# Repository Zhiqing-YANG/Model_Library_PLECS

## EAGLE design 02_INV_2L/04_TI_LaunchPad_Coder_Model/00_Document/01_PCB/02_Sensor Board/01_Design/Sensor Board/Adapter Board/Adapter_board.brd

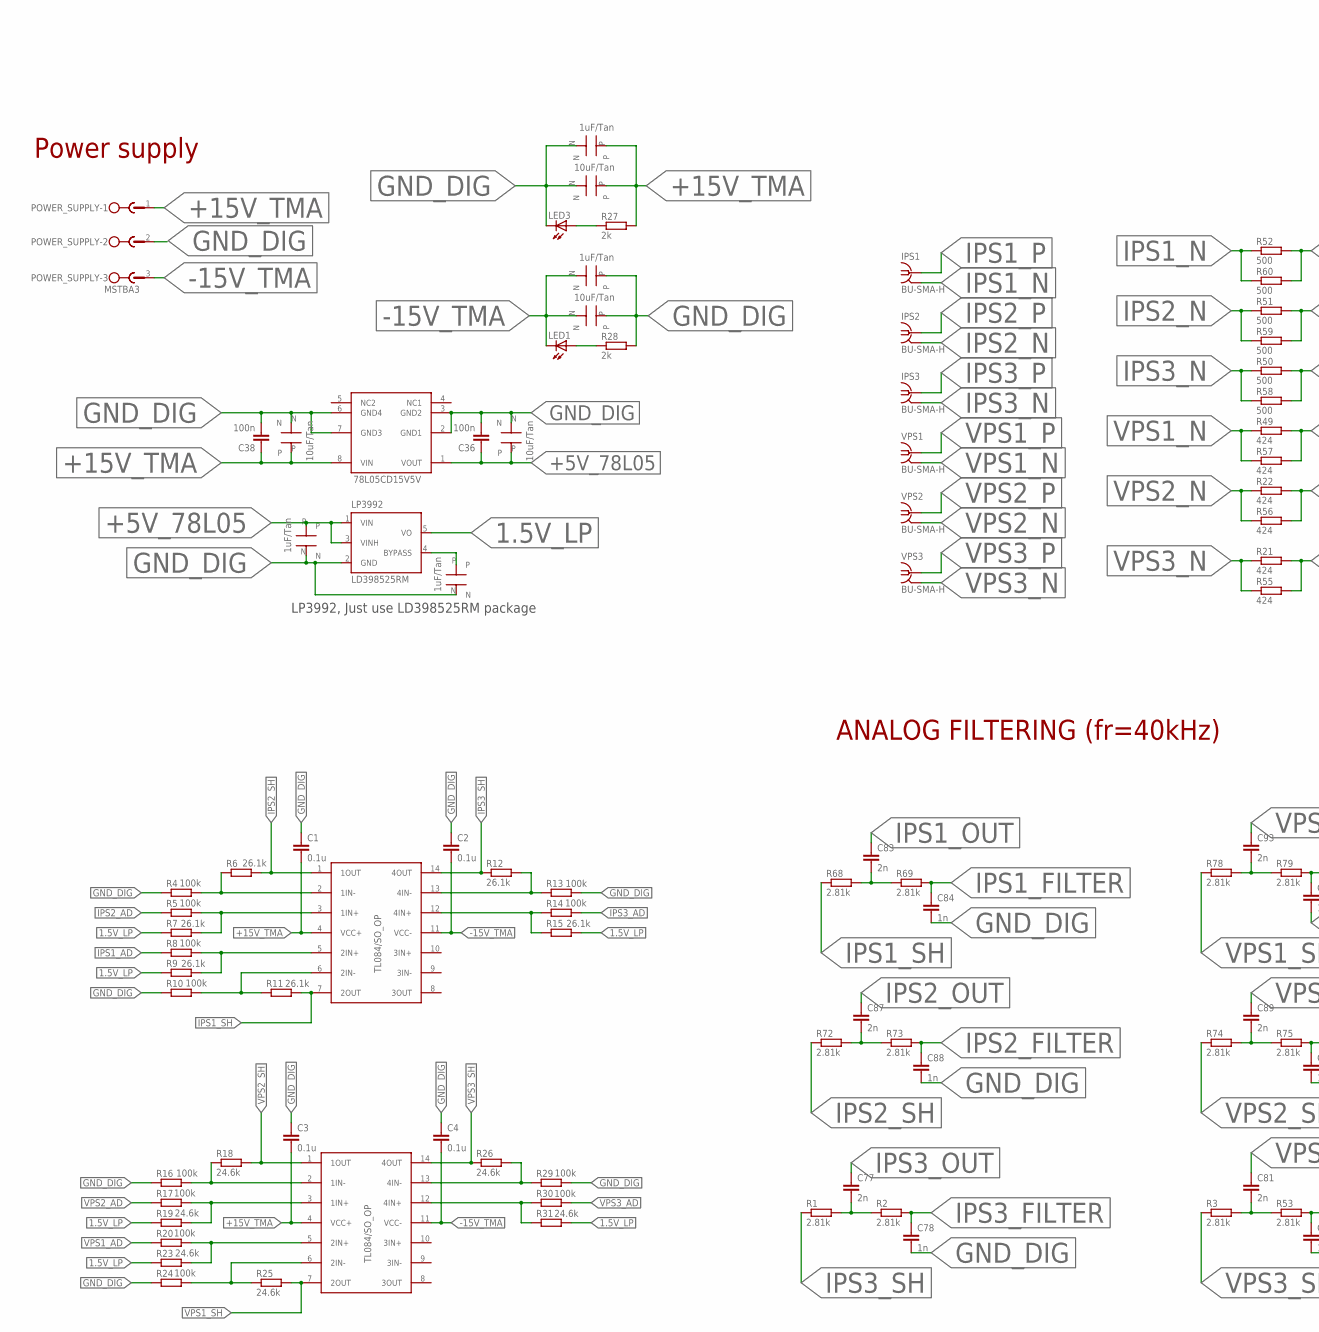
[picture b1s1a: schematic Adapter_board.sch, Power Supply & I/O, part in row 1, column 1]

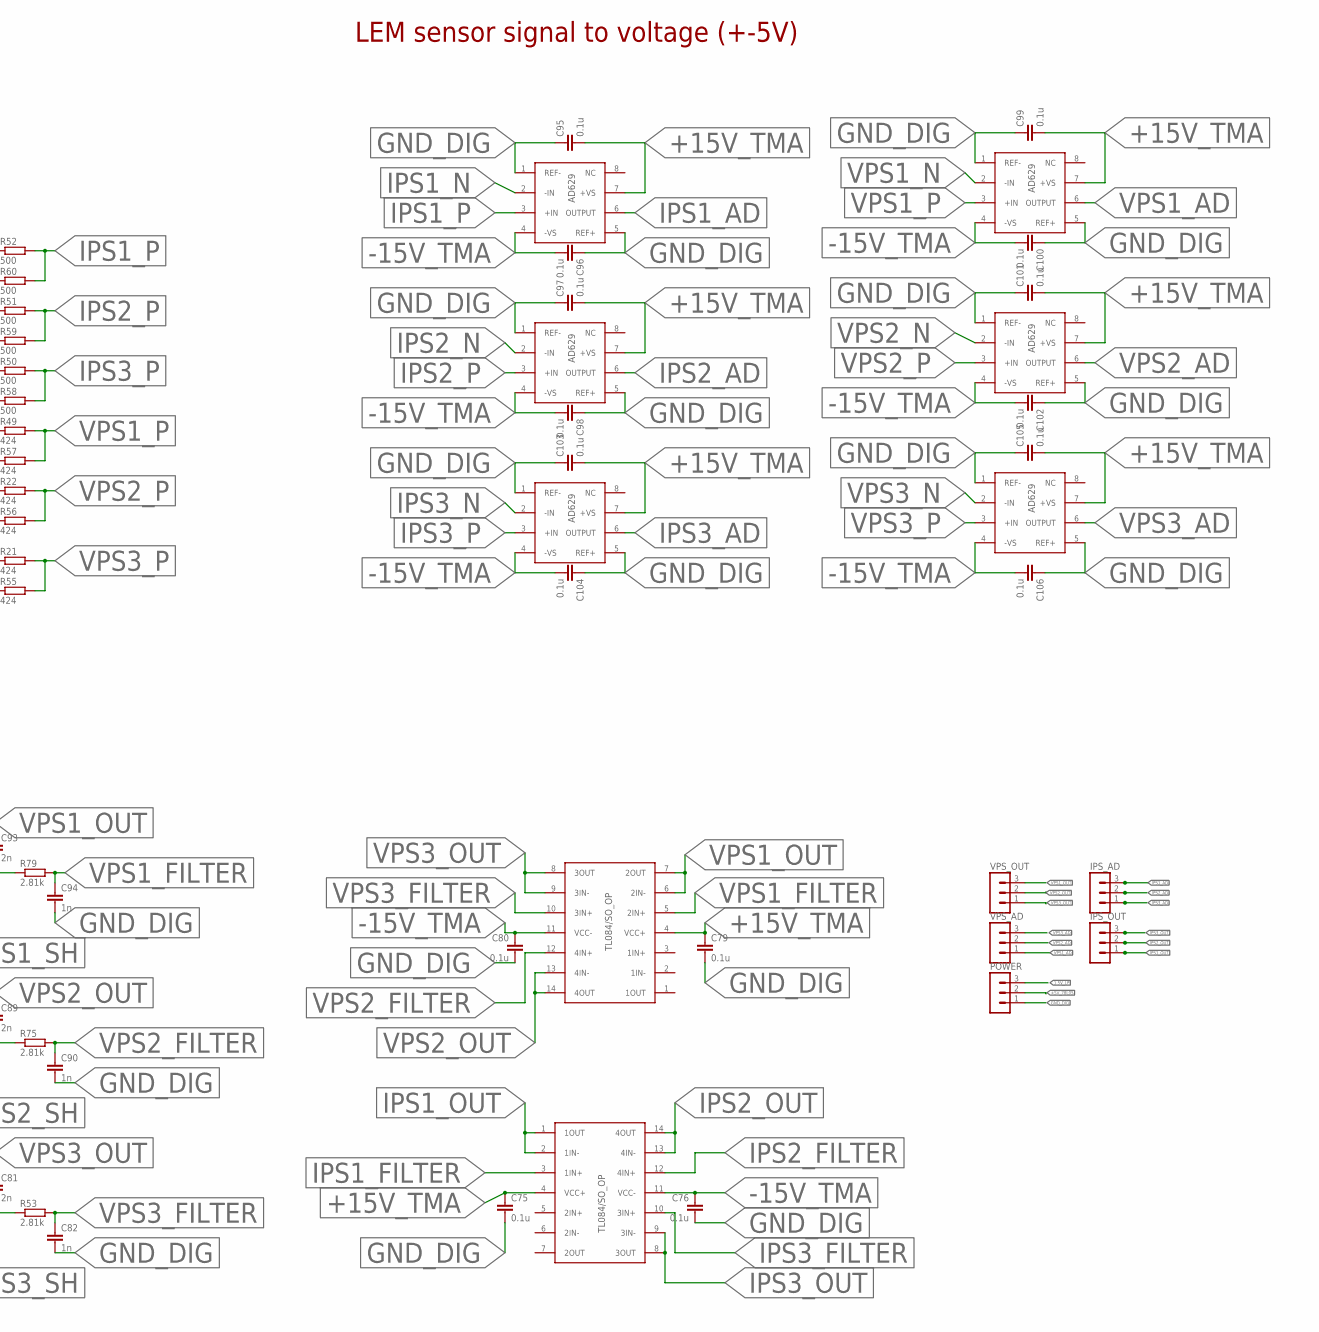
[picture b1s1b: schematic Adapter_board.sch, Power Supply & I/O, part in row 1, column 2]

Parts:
78L05: 78L05CD15V5VONLINE; 78L05CD15V5V_LIB
C1, C2, C3, C4, C75, C76, C79, C80, C95, C96, C97, C98, C99, C100, C101, C102, C103, C104, C105, C106: 0.1u; C0805
C36, C38: 100n; C0805
C37: TANTALUM_C_10UF_KEM
C77, C81, C83, C87, C89, C93: 2n; C0805
C78, C82, C84, C88, C90, C94: 1n; C0805
IPS1, IPS2, IPS3: BU-SMA-H
IPS_AD: MA03-1
IPS_OUT: MA03-1
LED1, LED3: LEDCHIPLED_0805; CHIPLED_0805
LP3992: LD398525RM; SOT23-5L
POWER: MA03-1
POWER_SUPPLY: MSTBA3
R1, R2, R3, R53, R68, R69, R72, R73, R74, R75, R78, R79: 2.81k; R0805
R4, R5, R8, R10, R13, R14, R16, R17, R20, R24, R29, R30: 100k; R0805
R6, R7, R9, R11, R12, R15: 26.1k; R0805
R18, R19, R23, R25, R26, R31: 24.6k; R0805
R21, R22, R49, R55, R56, R57: 424; R1206
R27, R28: 2k; R0805
R50, R51, R52, R58, R59, R60: 500; R1206
U$1, U$2, U$4, U$6: TL084/SO_OPONLINE; TL084/SO_OP_LIB
U$3, U$5, U$10, U$12: TANTALUM_C_1UF_KEMTANTALUM_C_1UF_KEM; TANTALUM_C_1UF_KEM
U$11, U$14, U$66: TANTALUM_C_10UF_KEM
U$24, U$27, U$28, U$29, U$30, U$31: AD629_DIFFAONLINE; AD629_DIFFA_LIB
VPS1, VPS2, VPS3: BU-SMA-H
VPS_AD: MA03-1
VPS_OUT: MA03-1

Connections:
1.5V_LP: LP3992.5 (VO), POWER.3, R7.1, R9.1, R15.2, R19.1, R23.1, R31.2
+5V_78L05: 78L05.1 (VOUT), C36.1, C37.P, LP3992.1 (VIN), LP3992.3 (VINH), POWER.2, U$3.P
+15V_TMA: 78L05.8 (VIN), C1.2, C3.2, C38.1, C75.1, C79.1, C95.2, C97.2, C99.2, C101.2, C103.2, C105.2, POWER_SUPPLY.1, R27.2, U$1.4 (VCC+), U$2.4 (VCC+), U$4.4 (VCC+), U$6.4 (VCC+), U$10.P, U$11.P, U$24.7 (+VS), U$27.7 (+VS), U$28.7 (+VS), U$29.7 (+VS), U$30.7 (+VS), U$31.7 (+VS), U$66.P
-15V_TMA: C2.2, C4.2, C76.1, C80.1, C96.2, C98.2, C100.2, C102.2, C104.2, C106.2, LED1.C, POWER_SUPPLY.3, U$1.11 (VCC-), U$2.11 (VCC-), U$4.11 (VCC-), U$6.11 (VCC-), U$12.N, U$14.N, U$24.4 (-VS), U$27.4 (-VS), U$28.4 (-VS), U$29.4 (-VS), U$30.4 (-VS), U$31.4 (-VS)
GND_DIG: 78L05.2 (GND1), 78L05.3 (GND2), 78L05.6 (GND4), 78L05.7 (GND3), C1.1, C2.1, C3.1, C4.1, C36.2, C37.N, C38.2, C75.2, C76.2, C78.2, C79.2, C80.2, C82.2, C84.2, C88.2, C90.2, C94.2, C95.1, C96.1, C97.1, C98.1, C99.1, C100.1, C101.1, C102.1, C103.1, C104.1, C105.1, C106.1, LED3.C, LP3992.2 (GND), POWER.1, POWER_SUPPLY.2, R4.1, R10.1, R13.2, R16.1, R24.1, R28.2, R29.2, U$3.N, U$5.N, U$10.N, U$11.N, U$12.P, U$14.P, U$24.1 (REF-), U$24.5 (REF+), U$27.1 (REF-), U$27.5 (REF+), U$28.1 (REF-), U$28.5 (REF+), U$29.1 (REF-), U$29.5 (REF+), U$30.1 (REF-), U$30.5 (REF+), U$31.1 (REF-), U$31.5 (REF+), U$66.N
IPS1_AD: IPS_AD.3, R8.1, U$24.6 (OUTPUT)
IPS1_FILTER: C84.1, R69.2, U$4.3 (1IN+)
IPS1_N: IPS1.2, IPS1.3 (2), IPS1.4 (2), IPS1.5 (2), R52.1, R60.1, U$24.2 (-IN)
IPS1_OUT: C83.1, IPS_OUT.1, U$4.1 (1OUT), U$4.2 (1IN-)
IPS1_P: IPS1.1, R52.2, R60.2, U$24.3 (+IN)
IPS1_SH: R11.2, R68.1, U$1.7 (2OUT)
IPS2_AD: IPS_AD.2, R5.1, U$27.6 (OUTPUT)
IPS2_FILTER: C88.1, R73.2, U$4.12 (4IN+)
IPS2_N: IPS2.2, IPS2.3 (2), IPS2.4 (2), IPS2.5 (2), R51.1, R59.1, U$27.2 (-IN)
IPS2_OUT: C87.1, IPS_OUT.2, U$4.13 (4IN-), U$4.14 (4OUT)
IPS2_P: IPS2.1, R51.2, R59.2, U$27.3 (+IN)
IPS2_SH: R6.2, R72.1, U$1.1 (1OUT)
IPS3_AD: IPS_AD.1, R14.2, U$30.6 (OUTPUT)
IPS3_FILTER: C78.1, R2.2, U$4.10 (3IN+)
IPS3_N: IPS3.2, IPS3.3 (2), IPS3.4 (2), IPS3.5 (2), R50.1, R58.1, U$30.2 (-IN)
IPS3_OUT: C77.1, IPS_OUT.3, U$4.8 (3OUT), U$4.9 (3IN-)
IPS3_P: IPS3.1, R50.2, R58.2, U$30.3 (+IN)
IPS3_SH: R1.1, R12.1, U$1.14 (4OUT)
unnamed: LP3992.4 (BYPASS), U$5.P
unnamed: R4.2, R6.1, U$1.2 (1IN-)
unnamed: R5.2, R7.2, U$1.3 (1IN+)
unnamed: R16.2, R18.1, U$2.2 (1IN-)
unnamed: R10.2, R11.1, U$1.6 (2IN-)
unnamed: R8.2, R9.2, U$1.5 (2IN+)
unnamed: R17.2, R19.2, U$2.3 (1IN+)
unnamed: C77.2, R1.2, R2.1
unnamed: C81.2, R3.2, R53.1
unnamed: C83.2, R68.2, R69.1
unnamed: LED3.A, R27.1
unnamed: LED1.A, R28.1
unnamed: C87.2, R72.2, R73.1
unnamed: R20.2, R23.2, U$2.5 (2IN+)
unnamed: C89.2, R74.2, R75.1
unnamed: C93.2, R78.2, R79.1
unnamed: R12.2, R13.1, U$1.13 (4IN-)
unnamed: R14.1, R15.1, U$1.12 (4IN+)
unnamed: R24.2, R25.1, U$2.6 (2IN-)
unnamed: R26.2, R29.1, U$2.13 (4IN-)
unnamed: R30.1, R31.1, U$2.12 (4IN+)
VPS1_AD: R20.1, U$28.6 (OUTPUT), VPS_AD.1
VPS1_FILTER: C94.1, R79.2, U$6.5 (2IN+)
VPS1_N: R49.1, R57.1, U$28.2 (-IN), VPS1.2, VPS1.3 (2), VPS1.4 (2), VPS1.5 (2)
VPS1_OUT: C93.1, U$6.6 (2IN-), U$6.7 (2OUT), VPS_OUT.3
VPS1_P: R49.2, R57.2, U$28.3 (+IN), VPS1.1
VPS1_SH: R25.2, R78.1, U$2.7 (2OUT)
VPS2_AD: R17.1, U$29.6 (OUTPUT), VPS_AD.2
VPS2_FILTER: C90.1, R75.2, U$6.12 (4IN+)
VPS2_N: R22.1, R56.1, U$29.2 (-IN), VPS2.2, VPS2.3 (2), VPS2.4 (2), VPS2.5 (2)
VPS2_OUT: C89.1, U$6.13 (4IN-), U$6.14 (4OUT), VPS_OUT.2
VPS2_P: R22.2, R56.2, U$29.3 (+IN), VPS2.1
VPS2_SH: R18.2, R74.1, U$2.1 (1OUT)
VPS3_AD: R30.2, U$31.6 (OUTPUT), VPS_AD.3
VPS3_FILTER: C82.1, R53.2, U$6.10 (3IN+)
VPS3_N: R21.1, R55.1, U$31.2 (-IN), VPS3.2, VPS3.3 (2), VPS3.4 (2), VPS3.5 (2)
VPS3_OUT: C81.1, U$6.8 (3OUT), U$6.9 (3IN-), VPS_OUT.1
VPS3_P: R21.2, R55.2, U$31.3 (+IN), VPS3.1
VPS3_SH: R3.1, R26.1, U$2.14 (4OUT)

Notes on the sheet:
Power supply
ANALOG FILTERING (fr=40kHz)
LEM sensor signal to voltage (+-5V)
LP3992, Just use LD398525RM package

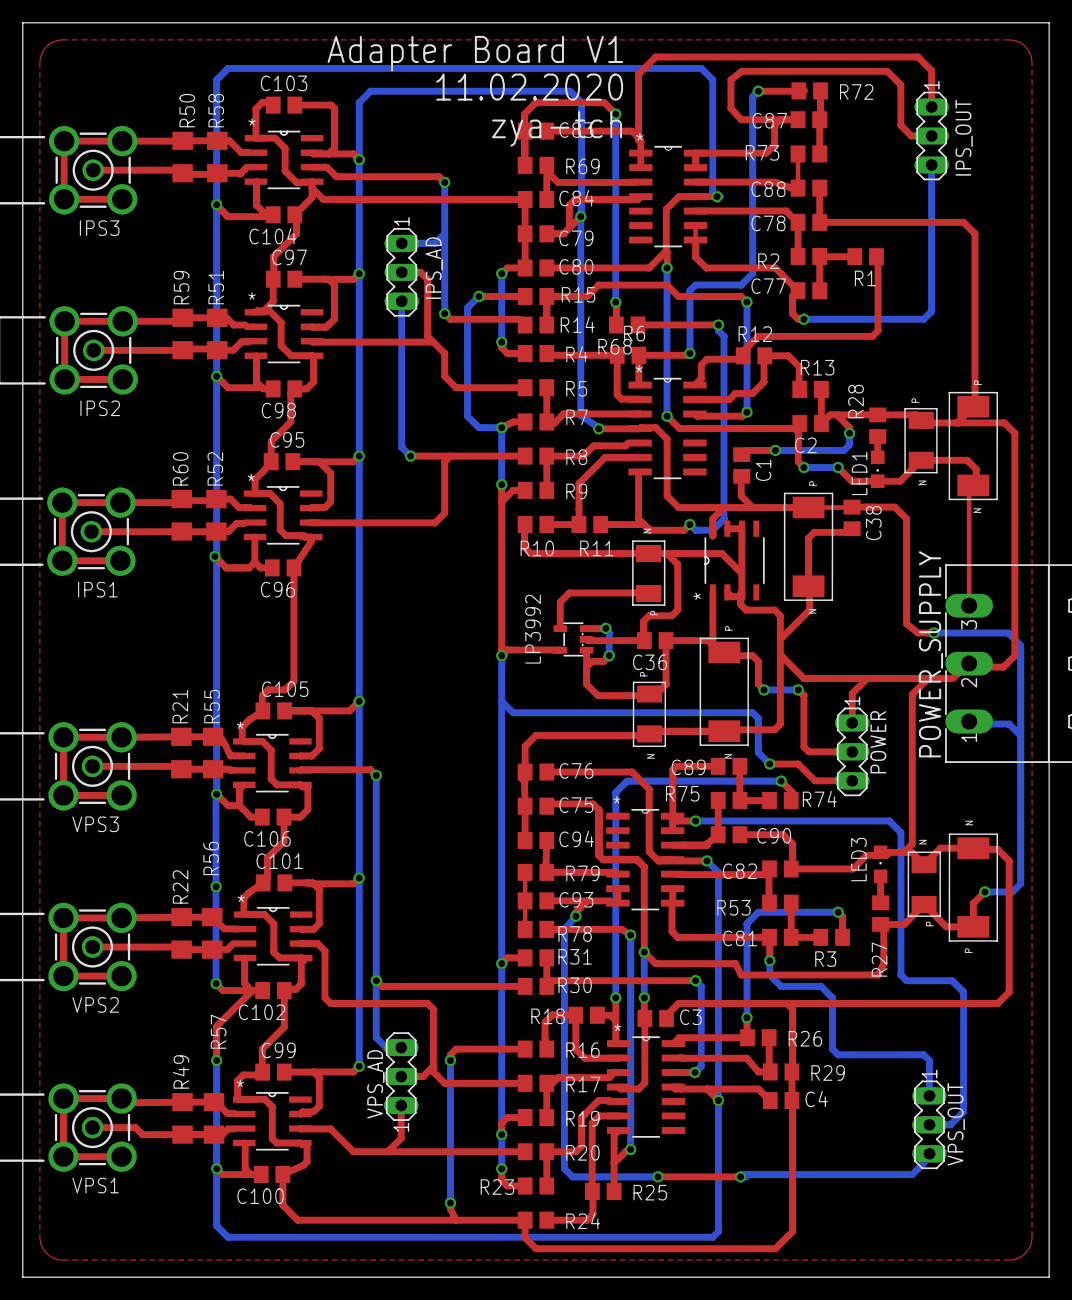
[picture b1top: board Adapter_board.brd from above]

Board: 2 copper layers, 90.0 x 110.0 mm, 118 parts (0 on the bottom side), 62 nets.

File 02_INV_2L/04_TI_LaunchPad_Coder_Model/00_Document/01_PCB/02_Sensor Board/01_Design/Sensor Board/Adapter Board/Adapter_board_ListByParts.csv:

"Part","Value","Attributes","Package","Description","Part Num"
"78L05","78L05CD15V5VONLINE","","78L05CD15V5V_LIB","78L05CD 15 V- 5 V voltage regulator","*"
"C1","0.1u","","C0805","CAPACITOR, European symbol","*"
"C2","0.1u","","C0805","CAPACITOR, European symbol","*"
"C3","0.1u","","C0805","CAPACITOR, European symbol","*"
"C4","0.1u","","C0805","CAPACITOR, European symbol","*"
"C36","100n","","C0805","CAPACITOR, European symbol","*"
"C37","TANTALUM_C_10UF_KEM","","TANTALUM_C_10UF_KEM","","*"
"C38","100n","","C0805","CAPACITOR, European symbol","*"
"C75","0.1u","","C0805","CAPACITOR, European symbol","*"
"C76","0.1u","","C0805","CAPACITOR, European symbol","*"
"C77","2n","","C0805","CAPACITOR, European symbol","*"
"C78","1n","","C0805","CAPACITOR, European symbol","*"
"C79","0.1u","","C0805","CAPACITOR, European symbol","*"
"C80","0.1u","","C0805","CAPACITOR, European symbol","*"
"C81","2n","","C0805","CAPACITOR, European symbol","*"
"C82","1n","","C0805","CAPACITOR, European symbol","*"
"C83","2n","","C0805","CAPACITOR, European symbol","*"
"C84","1n","","C0805","CAPACITOR, European symbol","*"
"C87","2n","","C0805","CAPACITOR, European symbol","*"
"C88","1n","","C0805","CAPACITOR, European symbol","*"
"C89","2n","","C0805","CAPACITOR, European symbol","*"
"C90","1n","","C0805","CAPACITOR, European symbol","*"
"C93","2n","","C0805","CAPACITOR, European symbol","*"
"C94","1n","","C0805","CAPACITOR, European symbol","*"
"C95","0.1u","","C0805","CAPACITOR, European symbol","*"
"C96","0.1u","","C0805","CAPACITOR, European symbol","*"
"C97","0.1u","","C0805","CAPACITOR, European symbol","*"
"C98","0.1u","","C0805","CAPACITOR, European symbol","*"
"C99","0.1u","","C0805","CAPACITOR, European symbol","*"
"C100","0.1u","","C0805","CAPACITOR, European symbol","*"
"C101","0.1u","","C0805","CAPACITOR, European symbol","*"
"C102","0.1u","","C0805","CAPACITOR, European symbol","*"
"C103","0.1u","","C0805","CAPACITOR, European symbol","*"
"C104","0.1u","","C0805","CAPACITOR, European symbol","*"
"C105","0.1u","","C0805","CAPACITOR, European symbol","*"
"C106","0.1u","","C0805","CAPACITOR, European symbol","*"
"IPS1","BU-SMA-H","","BU-SMA-H","FEMALE SMA CONNECTOR","*"
"IPS2","BU-SMA-H","","BU-SMA-H","FEMALE SMA CONNECTOR","*"
"IPS3","BU-SMA-H","","BU-SMA-H","FEMALE SMA CONNECTOR","*"
"IPS_AD","","","MA03-1","PIN HEADER","*"
"IPS_OUT","","","MA03-1","PIN HEADER","*"
"LED1","","","CHIPLED_0805","LED","*"
"LED3","","","CHIPLED_0805","LED","*"
"LP3992","LD398525RM","","SOT23-5L","Ultra low drop and low noise BiCMOS voltage regulators","*"
"POWER","","","MA03-1","PIN HEADER","*"
"POWER_SUPPLY","MSTBA3","","MSTBA3","PHOENIX","1757255"
"R1","2.81k","","R0805","RESISTOR, European symbol","*"
"R2","2.81k","","R0805","RESISTOR, European symbol","*"
"R3","2.81k","","R0805","RESISTOR, European symbol","*"
"R4","100k","","R0805","RESISTOR, European symbol","*"
"R5","100k","","R0805","RESISTOR, European symbol","*"
"R6","26.1k","","R0805","RESISTOR, European symbol","*"
"R7","26.1k","","R0805","RESISTOR, European symbol","*"
"R8","100k","","R0805","RESISTOR, European symbol","*"
"R9","26.1k","","R0805","RESISTOR, European symbol","*"
"R10","100k","","R0805","RESISTOR, European symbol","*"
"R11","26.1k","","R0805","RESISTOR, European symbol","*"
"R12","26.1k","","R0805","RESISTOR, European symbol","*"
"R13","100k","","R0805","RESISTOR, European symbol","*"
"R14","100k","","R0805","RESISTOR, European symbol","*"
"R15","26.1k","","R0805","RESISTOR, European symbol","*"
"R16","100k","","R0805","RESISTOR, European symbol","*"
"R17","100k","","R0805","RESISTOR, European symbol","*"
"R18","24.6k","","R0805","RESISTOR, European symbol","*"
"R19","24.6k","","R0805","RESISTOR, European symbol","*"
"R20","100k","","R0805","RESISTOR, European symbol","*"
"R21","424","","R1206","RESISTOR, European symbol","*"
"R22","424","","R1206","RESISTOR, European symbol","*"
"R23","24.6k","","R0805","RESISTOR, European symbol","*"
"R24","100k","","R0805","RESISTOR, European symbol","*"
"R25","24.6k","","R0805","RESISTOR, European symbol","*"
"R26","24.6k","","R0805","RESISTOR, European symbol","*"
"R27","2k","","R0805","RESISTOR, European symbol","*"
"R28","2k","","R0805","RESISTOR, European symbol","*"
"R29","100k","","R0805","RESISTOR, European symbol","*"
"R30","100k","","R0805","RESISTOR, European symbol","*"
"R31","24.6k","","R0805","RESISTOR, European symbol","*"
"R49","424","","R1206","RESISTOR, European symbol","*"
"R50","500","","R1206","RESISTOR, European symbol","*"
"R51","500","","R1206","RESISTOR, European symbol","*"
"R52","500","","R1206","RESISTOR, European symbol","*"
"R53","2.81k","","R0805","RESISTOR, European symbol","*"
"R55","424","","R1206","RESISTOR, European symbol","*"
"R56","424","","R1206","RESISTOR, European symbol","*"
"R57","424","","R1206","RESISTOR, European symbol","*"
"R58","500","","R1206","RESISTOR, European symbol","*"
"R59","500","","R1206","RESISTOR, European symbol","*"
"R60","500","","R1206","RESISTOR, European symbol","*"
"R68","2.81k","","R0805","RESISTOR, European symbol","*"
"R69","2.81k","","R0805","RESISTOR, European symbol","*"
"R72","2.81k","","R0805","RESISTOR, European symbol","*"
"R73","2.81k","","R0805","RESISTOR, European symbol","*"
"R74","2.81k","","R0805","RESISTOR, European symbol","*"
"R75","2.81k","","R0805","RESISTOR, European symbol","*"
"R78","2.81k","","R0805","RESISTOR, European symbol","*"
"R79","2.81k","","R0805","RESISTOR, European symbol","*"
"U$1","TL084/SO_OPONLINE","","TL084/SO_OP_LIB","","*"
"U$2","TL084/SO_OPONLINE","","TL084/SO_OP_LIB","","*"
"U$3","TANTALUM_C_1UF_KEMTANTALUM_C_1UF_KEM","","TANTALUM_C_1UF_KEM","","*"
"U$4","TL084/SO_OPONLINE","","TL084/SO_OP_LIB","","*"
"U$5","TANTALUM_C_1UF_KEMTANTALUM_C_1UF_KEM","","TANTALUM_C_1UF_KEM","","*"
"U$6","TL084/SO_OPONLINE","","TL084/SO_OP_LIB","","*"
"U$10","TANTALUM_C_1UF_KEMTANTALUM_C_1UF_KEM","","TANTALUM_C_1UF_KEM","","*"
"U$11","TANTALUM_C_10UF_KEM","","TANTALUM_C_10UF_KEM","","*"
"U$12","TANTALUM_C_1UF_KEMTANTALUM_C_1UF_KEM","","TANTALUM_C_1UF_KEM","","*"
"U$14","TANTALUM_C_10UF_KEM","","TANTALUM_C_10UF_KEM","","*"
"U$24","AD629_DIFFAONLINE","","AD629_DIFFA_LIB","","*"
"U$27","AD629_DIFFAONLINE","","AD629_DIFFA_LIB","","*"
"U$28","AD629_DIFFAONLINE","","AD629_DIFFA_LIB","","*"
"U$29","AD629_DIFFAONLINE","","AD629_DIFFA_LIB","","*"
"U$30","AD629_DIFFAONLINE","","AD629_DIFFA_LIB","","*"
"U$31","AD629_DIFFAONLINE","","AD629_DIFFA_LIB","","*"
"U$66","TANTALUM_C_10UF_KEM","","TANTALUM_C_10UF_KEM","","*"
"VPS1","BU-SMA-H","","BU-SMA-H","FEMALE SMA CONNECTOR","*"
"VPS2","BU-SMA-H","","BU-SMA-H","FEMALE SMA CONNECTOR","*"
"VPS3","BU-SMA-H","","BU-SMA-H","FEMALE SMA CONNECTOR","*"
"VPS_AD","","","MA03-1","PIN HEADER","*"
"VPS_OUT","","","MA03-1","PIN HEADER","*"

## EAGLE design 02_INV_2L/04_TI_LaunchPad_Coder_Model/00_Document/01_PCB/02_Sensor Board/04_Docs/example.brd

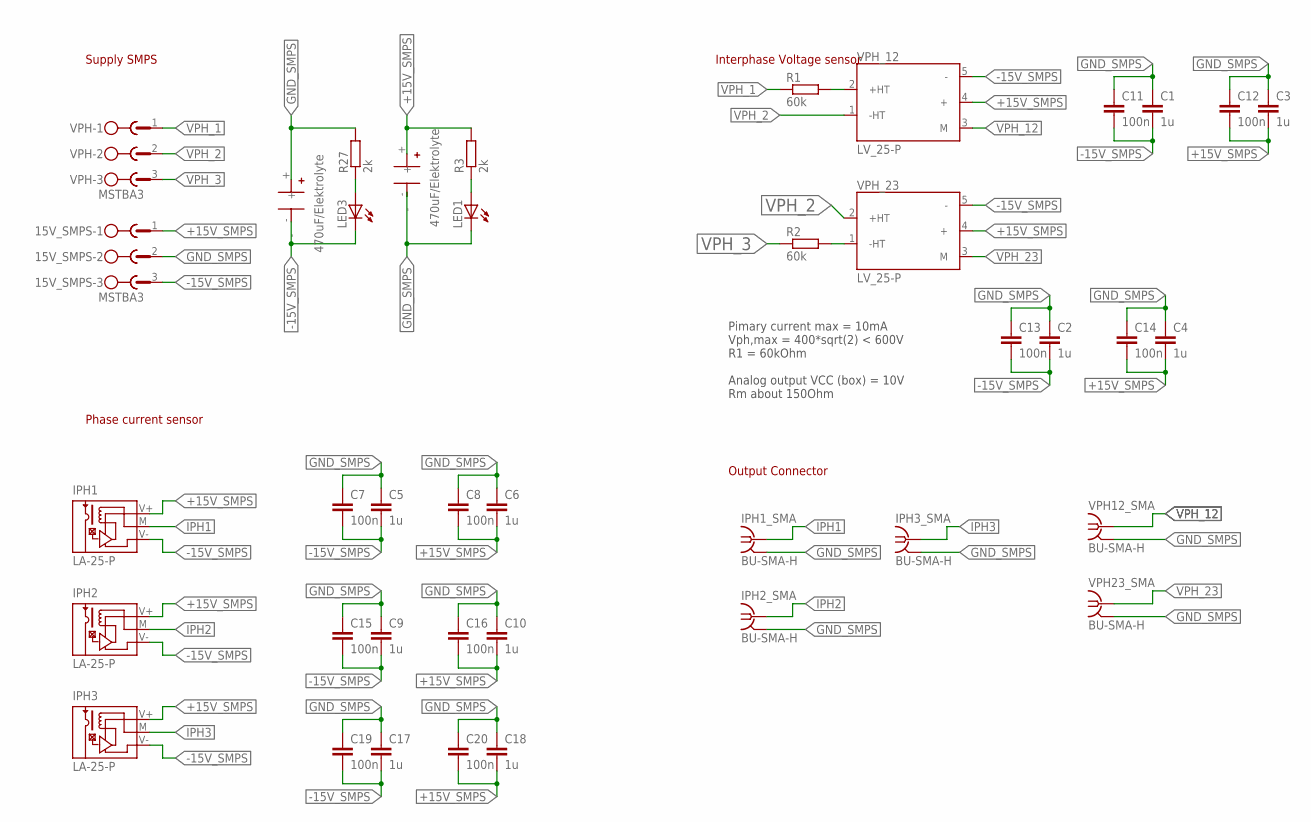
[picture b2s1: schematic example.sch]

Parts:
15V_SMPS: MSTBA3
C1, C2, C3, C4, C5, C6, C9, C10, C17, C18: 1u; C0805
C7, C8, C11, C12, C13, C14, C15, C16, C19, C20: 100n; C0805
IPH1, IPH2, IPH3: LA-25-P; LA25P
IPH1_SMA, IPH2_SMA, IPH3_SMA: BU-SMA-H
LED1, LED3: LEDCHIPLED_0805; CHIPLED_0805
R1, R2: 60k; 0414/15
R3, R27: 2k; R0805
U$1, U$2: ELE_C_470UF_PAN; ELEK_C_470UF_PAN
VPH: MSTBA3
VPH12_SMA, VPH23_SMA: BU-SMA-H
VPH_12, VPH_23: LV_25-P; XDCR_LV25-P

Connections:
+15V_SMPS: 15V_SMPS.1, C3.2, C4.2, C6.2, C8.2, C10.2, C12.2, C14.2, C16.2, C18.2, C20.2, IPH1.V+, IPH2.V+, IPH3.V+, R3.2, U$2.+, VPH_12.4 (+), VPH_23.4 (+)
-15V_SMPS: 15V_SMPS.3, C1.2, C2.2, C5.2, C7.2, C9.2, C11.2, C13.2, C15.2, C17.2, C19.2, IPH1.V-, IPH2.V-, IPH3.V-, LED3.C, U$1.-, VPH_12.5 (-), VPH_23.5 (-)
GND_SMPS: 15V_SMPS.2, C1.1, C2.1, C3.1, C4.1, C5.1, C6.1, C7.1, C8.1, C9.1, C10.1, C11.1, C12.1, C13.1, C14.1, C15.1, C16.1, C17.1, C18.1, C19.1, C20.1, IPH1_SMA.2, IPH1_SMA.3 (2), IPH1_SMA.4 (2), IPH1_SMA.5 (2), IPH2_SMA.2, IPH2_SMA.3 (2), IPH2_SMA.4 (2), IPH2_SMA.5 (2), IPH3_SMA.2, IPH3_SMA.3 (2), IPH3_SMA.4 (2), IPH3_SMA.5 (2), LED1.C, R27.2, U$1.+, U$2.-, VPH12_SMA.2, VPH12_SMA.3 (2), VPH12_SMA.4 (2), VPH12_SMA.5 (2), VPH23_SMA.2, VPH23_SMA.3 (2), VPH23_SMA.4 (2), VPH23_SMA.5 (2)
IPH1: IPH1.M, IPH1_SMA.1
IPH2: IPH2.M, IPH2_SMA.1
IPH3: IPH3.M, IPH3_SMA.1
unnamed: R1.2, VPH_12.2 (+HT)
unnamed: R2.2, VPH_23.1 (-HT)
unnamed: LED1.A, R3.1
unnamed: LED3.A, R27.1
VPH_1: R1.1, VPH.1
VPH_2: VPH.2, VPH_12.1 (-HT), VPH_23.2 (+HT)
VPH_3: R2.1, VPH.3
VPH_12: VPH12_SMA.1, VPH_12.3 (M)
VPH_23: VPH23_SMA.1, VPH_23.3 (M)

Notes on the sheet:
Pimary current max = 10mA Vph,max = 400*sqrt(2) < 600V R1 = 60kOhm Analog output VCC (box) = 10V Rm about 150Ohm
Supply SMPS
Interphase Voltage sensor
Phase current sensor
Output Connector

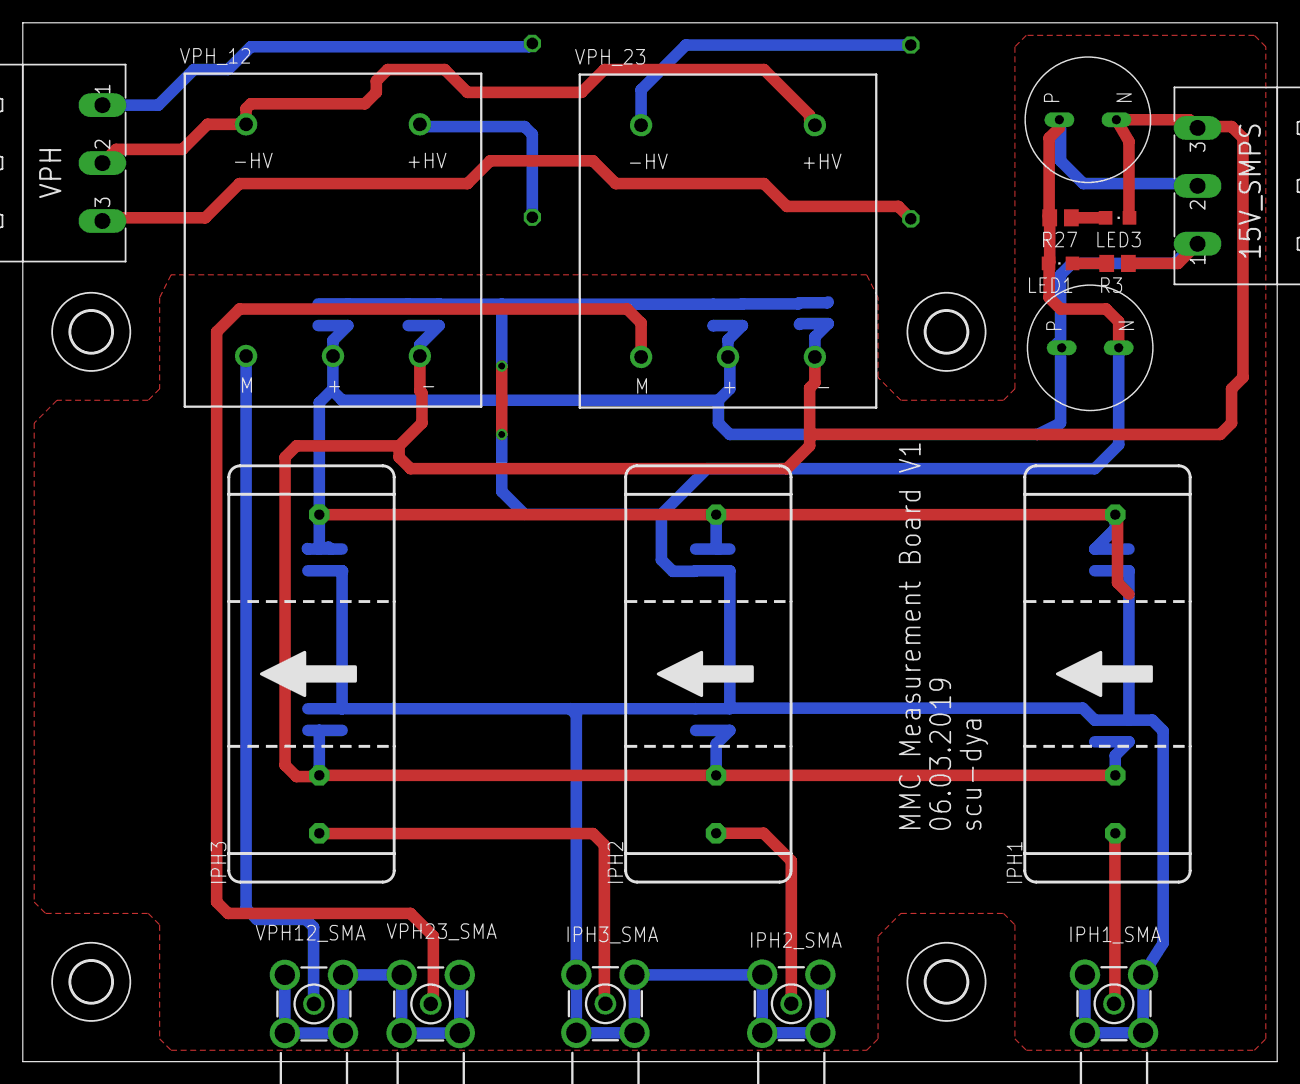
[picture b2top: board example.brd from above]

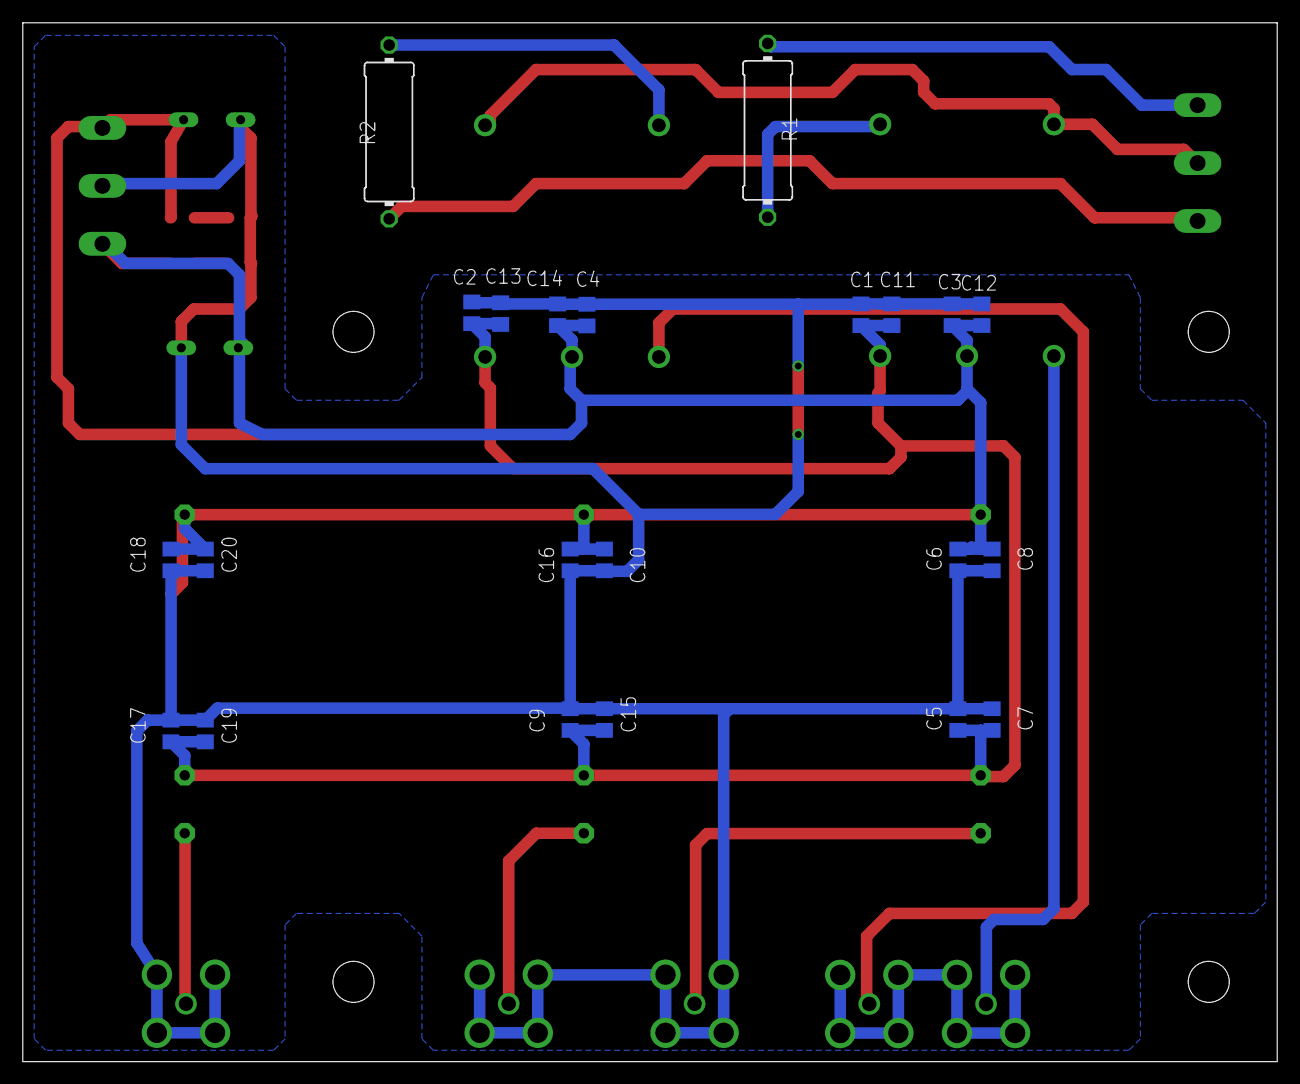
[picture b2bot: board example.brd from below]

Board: 2 copper layers, 110.0 x 91.1 mm, 44 parts (22 on the bottom side), 15 nets.

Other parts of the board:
U$4, U$5, U$8, U$12: 3,6

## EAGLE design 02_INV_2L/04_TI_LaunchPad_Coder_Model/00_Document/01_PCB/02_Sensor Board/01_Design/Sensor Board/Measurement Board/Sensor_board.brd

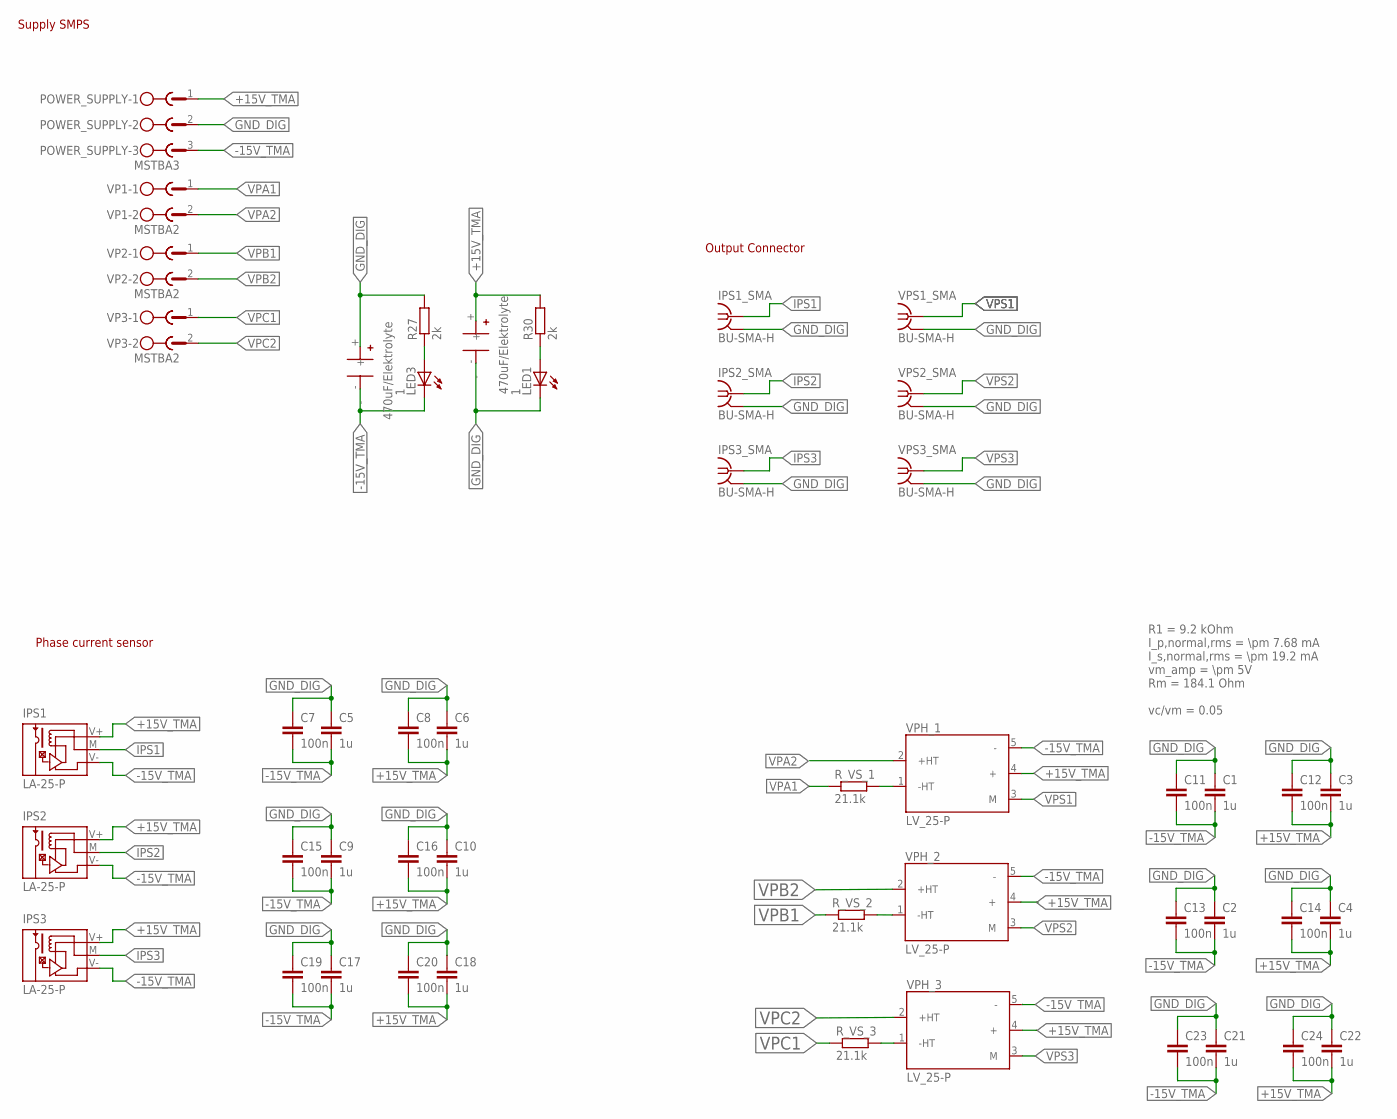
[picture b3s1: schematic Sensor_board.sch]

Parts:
C1, C2, C3, C4, C5, C6, C9, C10, C17, C18, C21, C22: 1u; C0805
C7, C8, C11, C12, C13, C14, C15, C16, C19, C20, C23, C24: 100n; C0805
C31, C32: ELE_C_470UF_PAN; ELEK_C_470UF_PAN
IPS1, IPS2, IPS3: LA-25-P; LA25P
IPS1_SMA, IPS2_SMA, IPS3_SMA: BU-SMA-H
LED1, LED3: 1; CHIPLED_0805
POWER_SUPPLY: MSTBA3
R27, R30: 2k; R0805
R_VS_1, R_VS_2, R_VS_3: 21.1k; 0414/15
VP1, VP2, VP3: MSTBA2
VPH_1, VPH_2, VPH_3: LV_25-P; XDCR_LV25-P
VPS1_SMA, VPS2_SMA, VPS3_SMA: BU-SMA-H

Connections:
+15V_TMA: C3.2, C4.2, C6.2, C8.2, C10.2, C12.2, C14.2, C16.2, C18.2, C20.2, C22.2, C24.2, C32.+, IPS1.V+, IPS2.V+, IPS3.V+, POWER_SUPPLY.1, R30.2, VPH_1.4 (+), VPH_2.4 (+), VPH_3.4 (+)
-15V_TMA: C1.2, C2.2, C5.2, C7.2, C9.2, C11.2, C13.2, C15.2, C17.2, C19.2, C21.2, C23.2, C31.-, IPS1.V-, IPS2.V-, IPS3.V-, LED3.C, POWER_SUPPLY.3, VPH_1.5 (-), VPH_2.5 (-), VPH_3.5 (-)
GND_DIG: C1.1, C2.1, C3.1, C4.1, C5.1, C6.1, C7.1, C8.1, C9.1, C10.1, C11.1, C12.1, C13.1, C14.1, C15.1, C16.1, C17.1, C18.1, C19.1, C20.1, C21.1, C22.1, C23.1, C24.1, C31.+, C32.-, IPS1_SMA.2, IPS1_SMA.3 (2), IPS1_SMA.4 (2), IPS1_SMA.5 (2), IPS2_SMA.2, IPS2_SMA.3 (2), IPS2_SMA.4 (2), IPS2_SMA.5 (2), IPS3_SMA.2, IPS3_SMA.3 (2), IPS3_SMA.4 (2), IPS3_SMA.5 (2), LED1.C, POWER_SUPPLY.2, R27.2, VPS1_SMA.2, VPS1_SMA.3 (2), VPS1_SMA.4 (2), VPS1_SMA.5 (2), VPS2_SMA.2, VPS2_SMA.3 (2), VPS2_SMA.4 (2), VPS2_SMA.5 (2), VPS3_SMA.2, VPS3_SMA.3 (2), VPS3_SMA.4 (2), VPS3_SMA.5 (2)
IPS1: IPS1.M, IPS1_SMA.1
IPS2: IPS2.M, IPS2_SMA.1
IPS3: IPS3.M, IPS3_SMA.1
unnamed: R_VS_1.2, VPH_1.1 (-HT)
unnamed: R_VS_2.2, VPH_2.1 (-HT)
unnamed: LED1.A, R30.1
unnamed: R_VS_3.2, VPH_3.1 (-HT)
unnamed: LED3.A, R27.1
VPA1: R_VS_1.1, VP1.1
VPA2: VP1.2, VPH_1.2 (+HT)
VPB1: R_VS_2.1, VP2.1
VPB2: VP2.2, VPH_2.2 (+HT)
VPC1: R_VS_3.1, VP3.1
VPC2: VP3.2, VPH_3.2 (+HT)
VPS1: VPH_1.3 (M), VPS1_SMA.1
VPS2: VPH_2.3 (M), VPS2_SMA.1
VPS3: VPH_3.3 (M), VPS3_SMA.1

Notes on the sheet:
Supply SMPS
Phase current sensor
Output Connector
R1 = 9.2 kOhm I_p,normal,rms = \pm 7.68 mA I_s,normal,rms = \pm 19.2 mA vm_amp = \pm 5V Rm = 184.1 Ohm vc/vm = 0.05
